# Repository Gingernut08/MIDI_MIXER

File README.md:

This project lets you use a physical 10-channel MIDI mixer to control the volume of individual apps on Windows. Each fader maps to a specific application, so you can change levels in real time without alt-tabbing or digging through volume sliders.
I built this because I wanted actual knobs and faders for my audio instead of fighting Windows every time Discord got loud.

Full Design

PCB

Wiring diagram

BOM

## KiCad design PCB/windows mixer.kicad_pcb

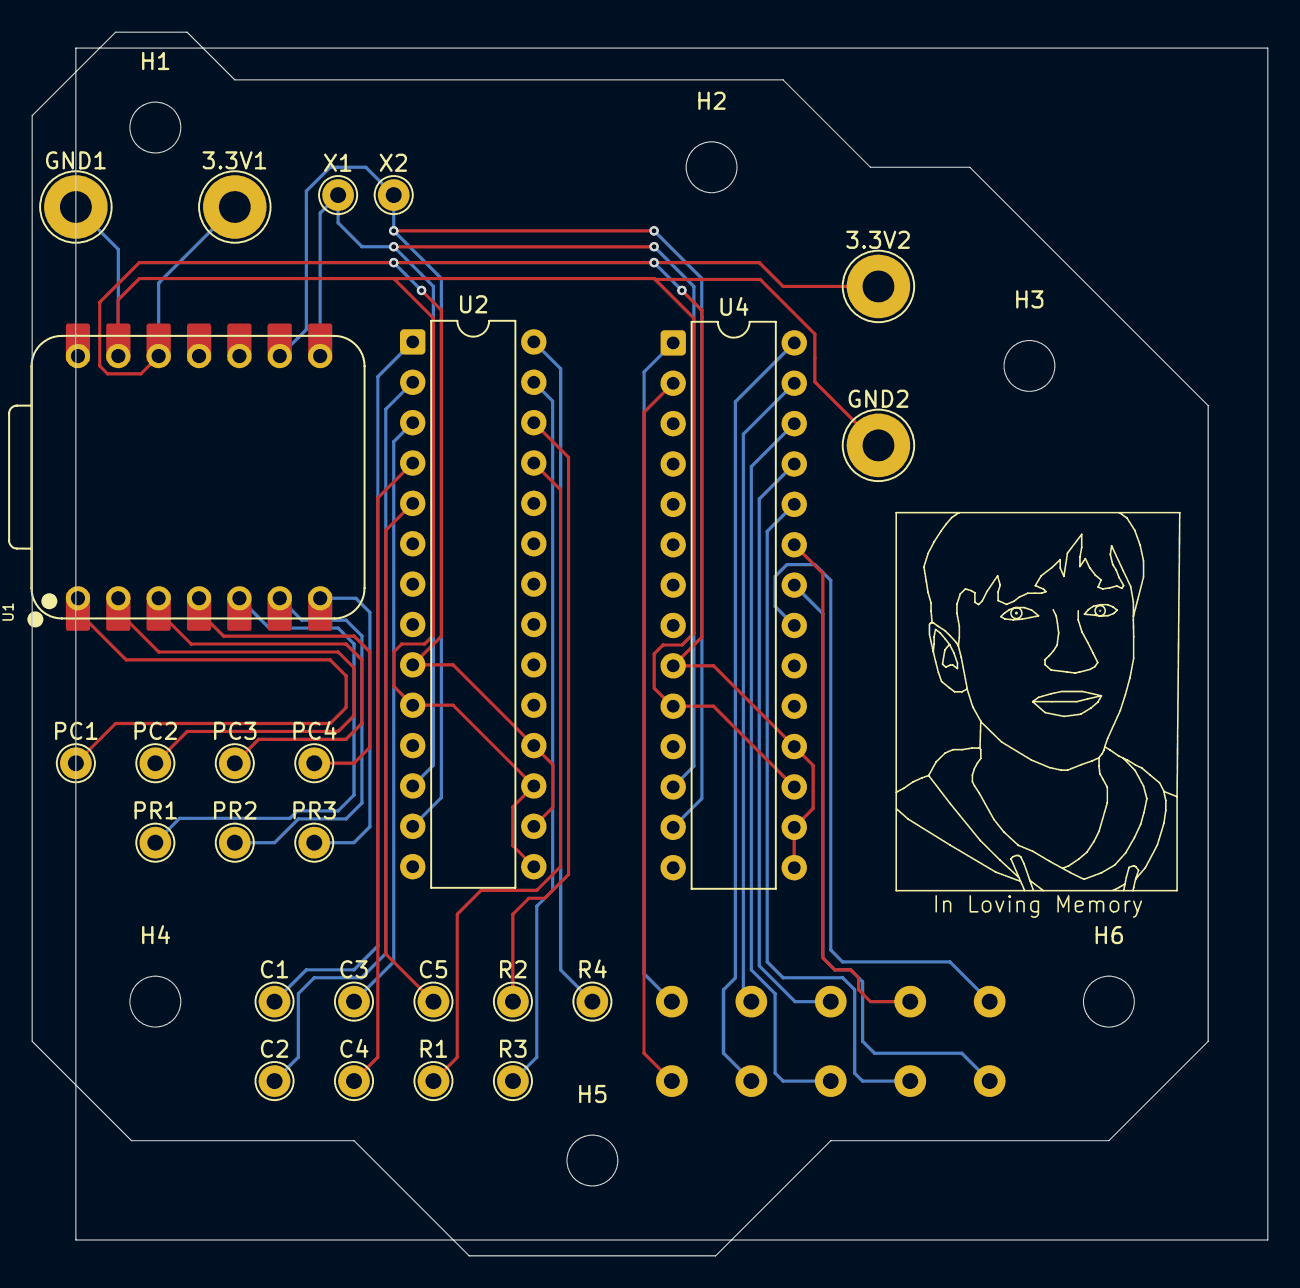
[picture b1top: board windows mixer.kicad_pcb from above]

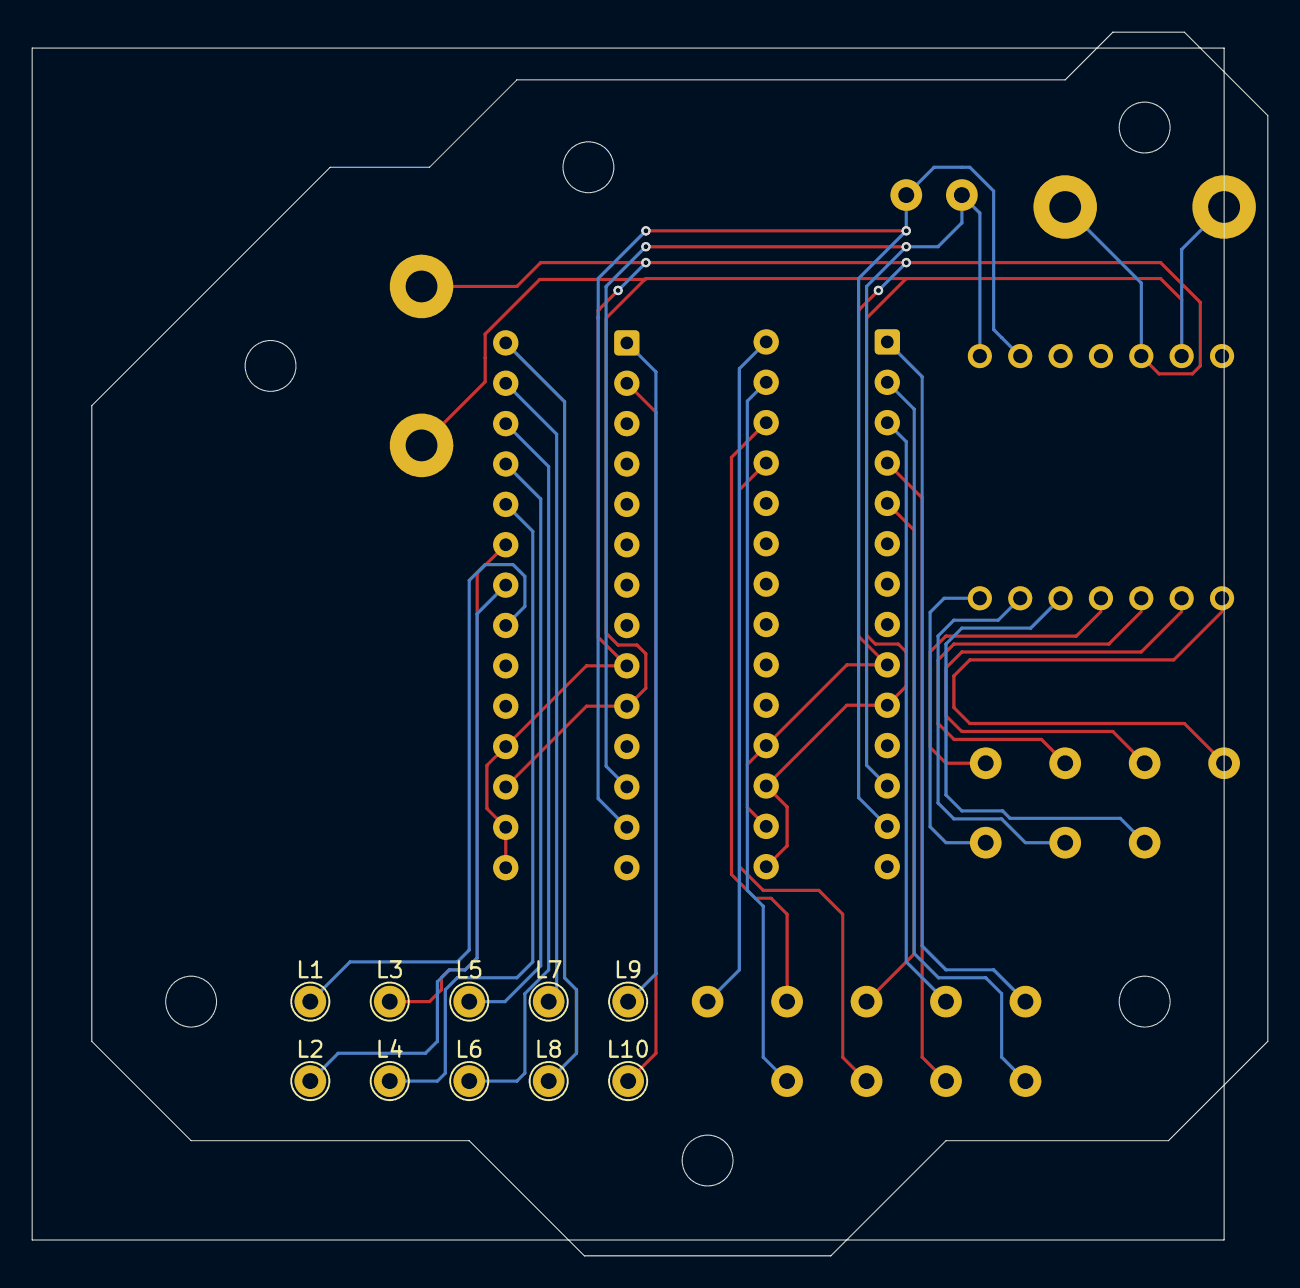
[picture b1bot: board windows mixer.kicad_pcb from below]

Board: 2 copper layers, 77.8 x 77.0 mm, 41 parts (10 on the bottom side), 30 nets.

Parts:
3.3V1, 3.3V2: TestPoint; TestPoint_THTPad_D4.0mm_Drill2.0mm
C1, C2, C3, C4, C5: TestPoint; TestPoint_THTPad_D2.0mm_Drill1.0mm
GND1, GND2: TestPoint; TestPoint_THTPad_D4.0mm_Drill2.0mm
H1, H2, H3, H4, H5, H6: MountingHole; MountingHole_3.2mm_M3
L1, L2, L3, L4, L5, L6, L7, L8, L9, L10: TestPoint; TestPoint_THTPad_D2.0mm_Drill1.0mm
PC1, PC2, PC3, PC4: TestPoint; TestPoint_THTPad_D2.0mm_Drill1.0mm
PR1, PR2, PR3: TestPoint; TestPoint_THTPad_D2.0mm_Drill1.0mm
R1, R2, R3, R4: TestPoint; TestPoint_THTPad_D2.0mm_Drill1.0mm
U1: XIAO-RP2040-DIP
U2, U4: MCP23017_SP; DIP-28_W7.62mm
X1, X2: TestPoint; TestPoint_THTPad_D2.0mm_Drill1.0mm

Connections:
+3.3V: 3.3V1.1, 3.3V2.1, U1.12 (3V3), U2.9 (VDD), U2.16 (A1), U2.18 (~RESET), U4.9 (VDD), U4.15 (A0), U4.16 (A1), U4.18 (~RESET)
/Expander_SCK: U1.8 (GPIO1/RX), U2.12 (SCK), U4.12 (SCK), X1.1
/Expander_SDA: U1.9 (GPIO2/SCK), U2.13 (SDA), U4.13 (SDA), X2.1
/Pot_Group_One: PR1.1, U1.5 (GPIO6/SDA)
/Pot_Group_Three: PR3.1, U1.7 (GPIO0/TX)
/Pot_Group_Two: PR2.1, U1.6 (GPIO7/SCL)
/Pot_Out_Four: PC4.1, U1.4 (GPIO29/ADC3/A3)
/Pot_Out_One: PC1.1, U1.1 (GPIO26/ADC0/A0)
/Pot_Out_Three: PC3.1, U1.3 (GPIO28/ADC2/A2)
/Pot_Out_Two: PC2.1, U1.2 (GPIO27/ADC1/A1)
GND: GND1.1, GND2.1, U1.13 (GND), U2.10 (VSS), U2.15 (A0), U2.17 (A2), U4.10 (VSS), U4.17 (A2)
unnamed: R1.1, U2.25 (GPA4)
unnamed: R2.1, U2.26 (GPA5)
unnamed: R3.1, U2.27 (GPA6)
unnamed: R4.1, U2.28 (GPA7)
unnamed: L1.1, U4.21 (GPA0)
unnamed: L2.1, U4.22 (GPA1)
unnamed: L3.1, U4.23 (GPA2)
unnamed: L4.1, U4.24 (GPA3)
unnamed: L5.1, U4.25 (GPA4)
unnamed: L6.1, U4.26 (GPA5)
unnamed: L7.1, U4.27 (GPA6)
unnamed: L8.1, U4.28 (GPA7)
unnamed: L9.1, U4.1 (GPB0)
unnamed: L10.1, U4.2 (GPB1)
unnamed: C1.1, U2.1 (GPB0)
unnamed: C2.1, U2.2 (GPB1)
unnamed: C3.1, U2.3 (GPB2)
unnamed: C4.1, U2.4 (GPB3)
unnamed: C5.1, U2.5 (GPB4)

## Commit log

2026-02-01 Add temporary file for filepath
2026-02-02 Initialize README with project details and images
    Added project description, design images, and diagrams.
2026-02-02 Update README with design and wiring images
    Added images for full design, PCB, wiring diagram, and BOM.
2026-02-12 Create filepath
